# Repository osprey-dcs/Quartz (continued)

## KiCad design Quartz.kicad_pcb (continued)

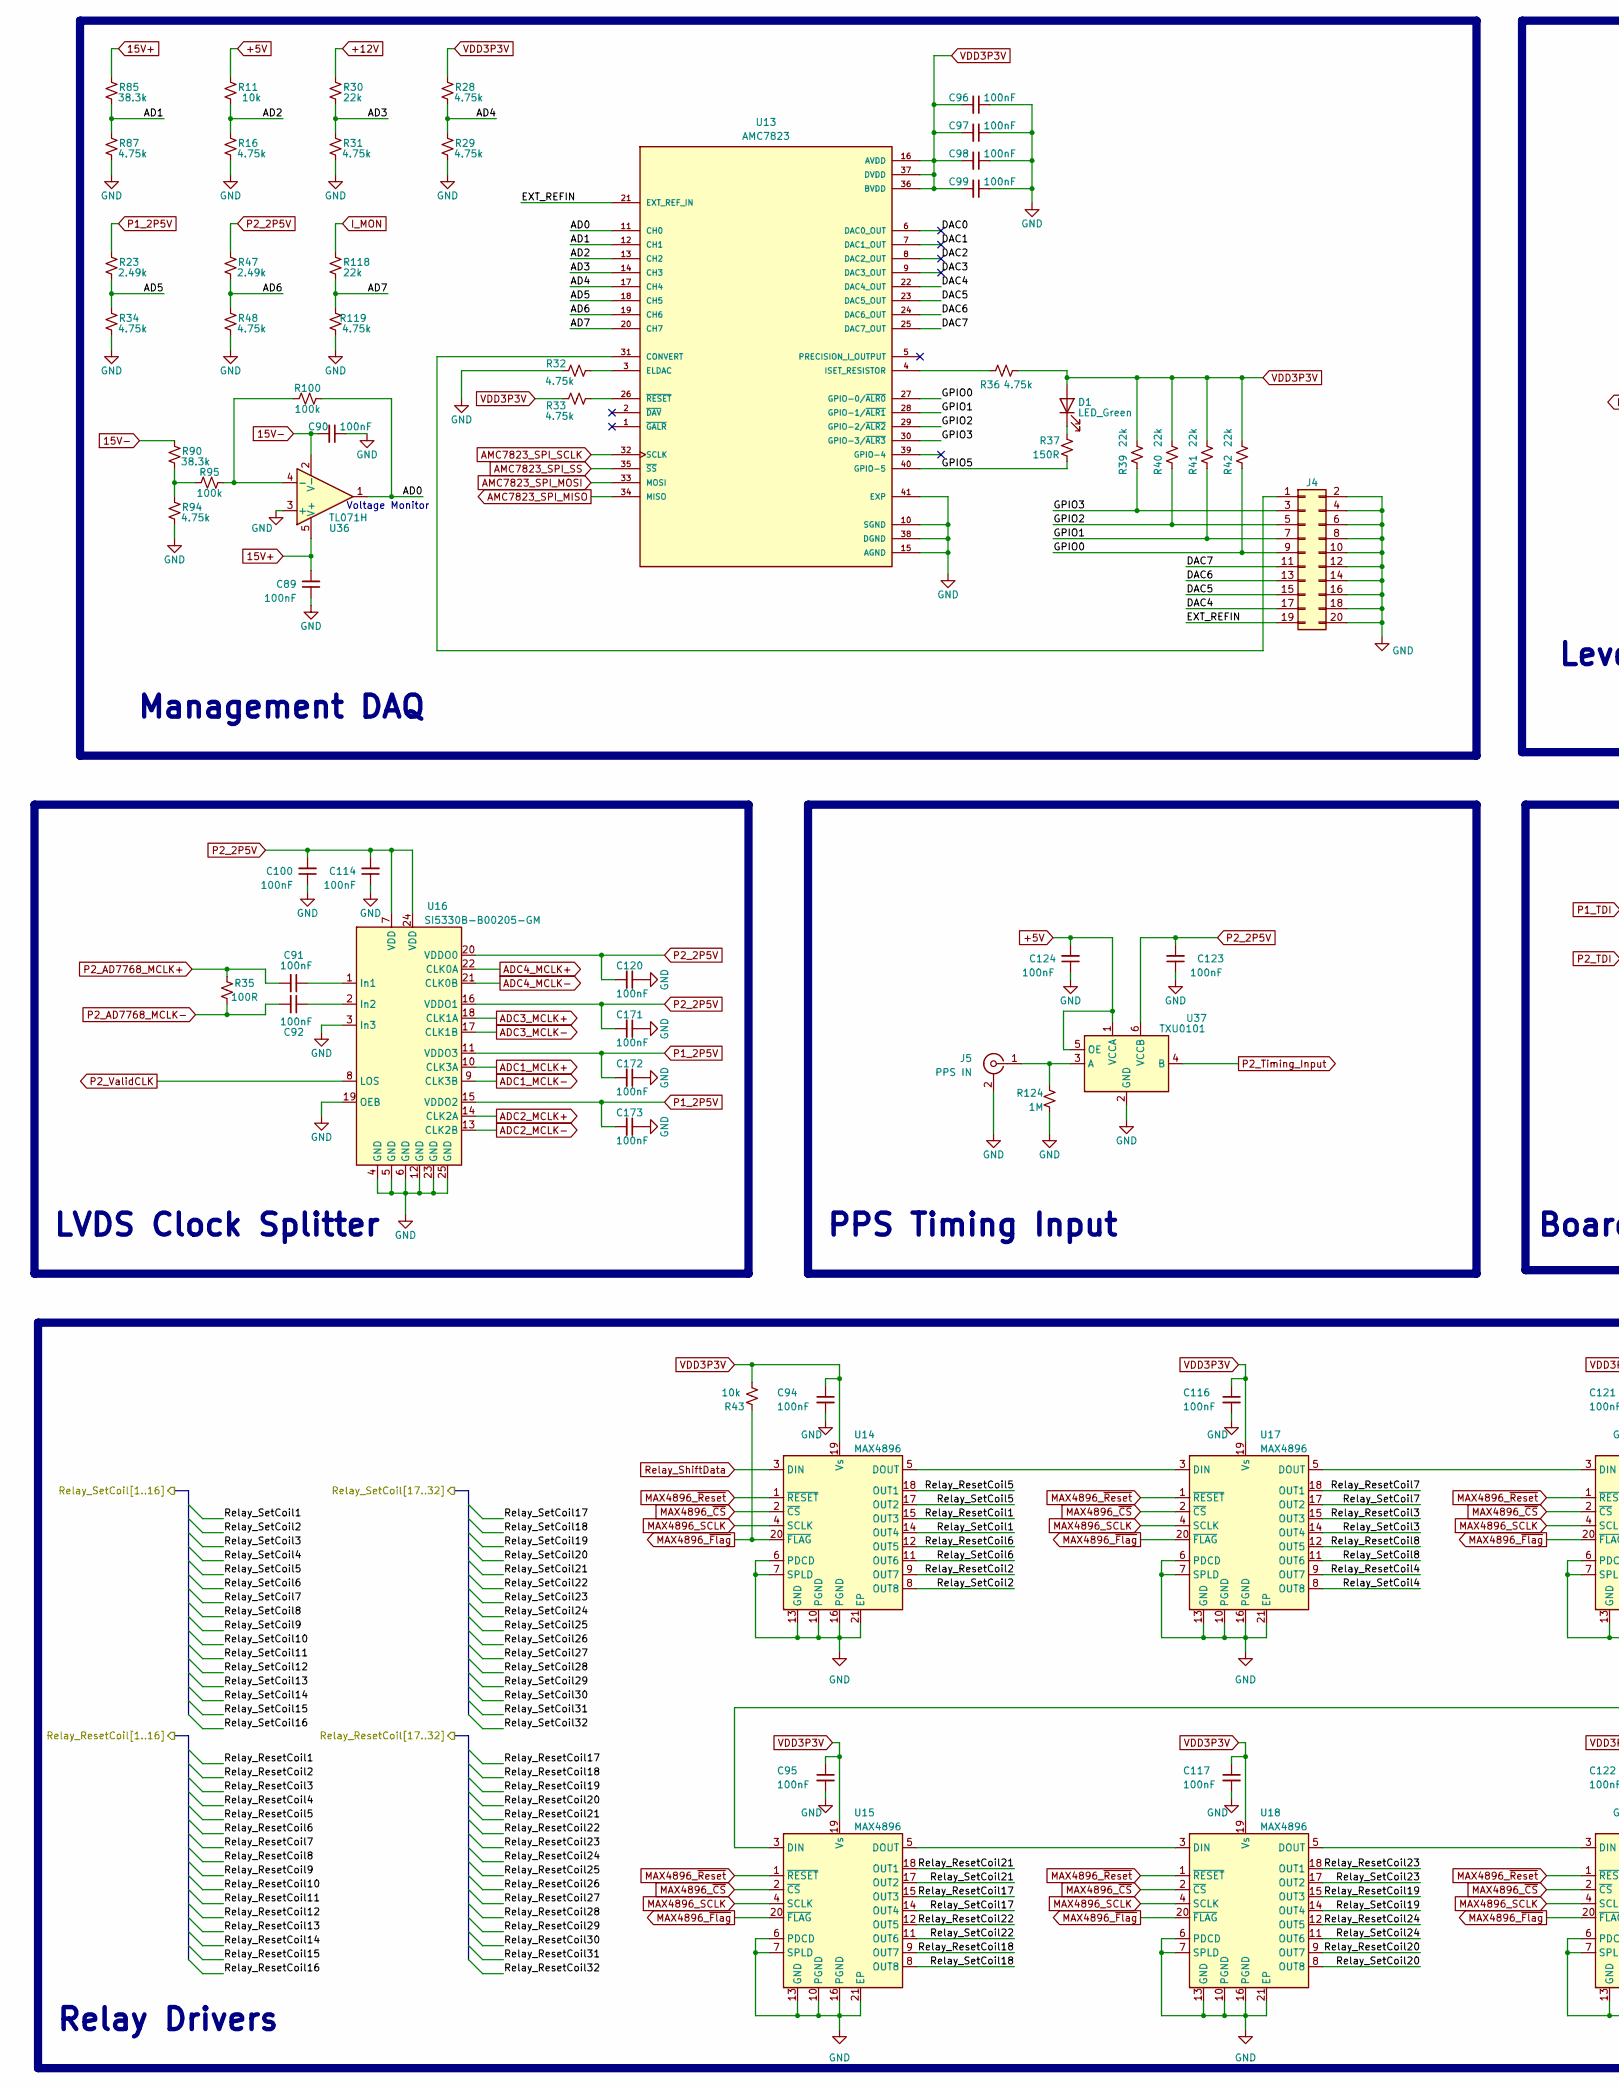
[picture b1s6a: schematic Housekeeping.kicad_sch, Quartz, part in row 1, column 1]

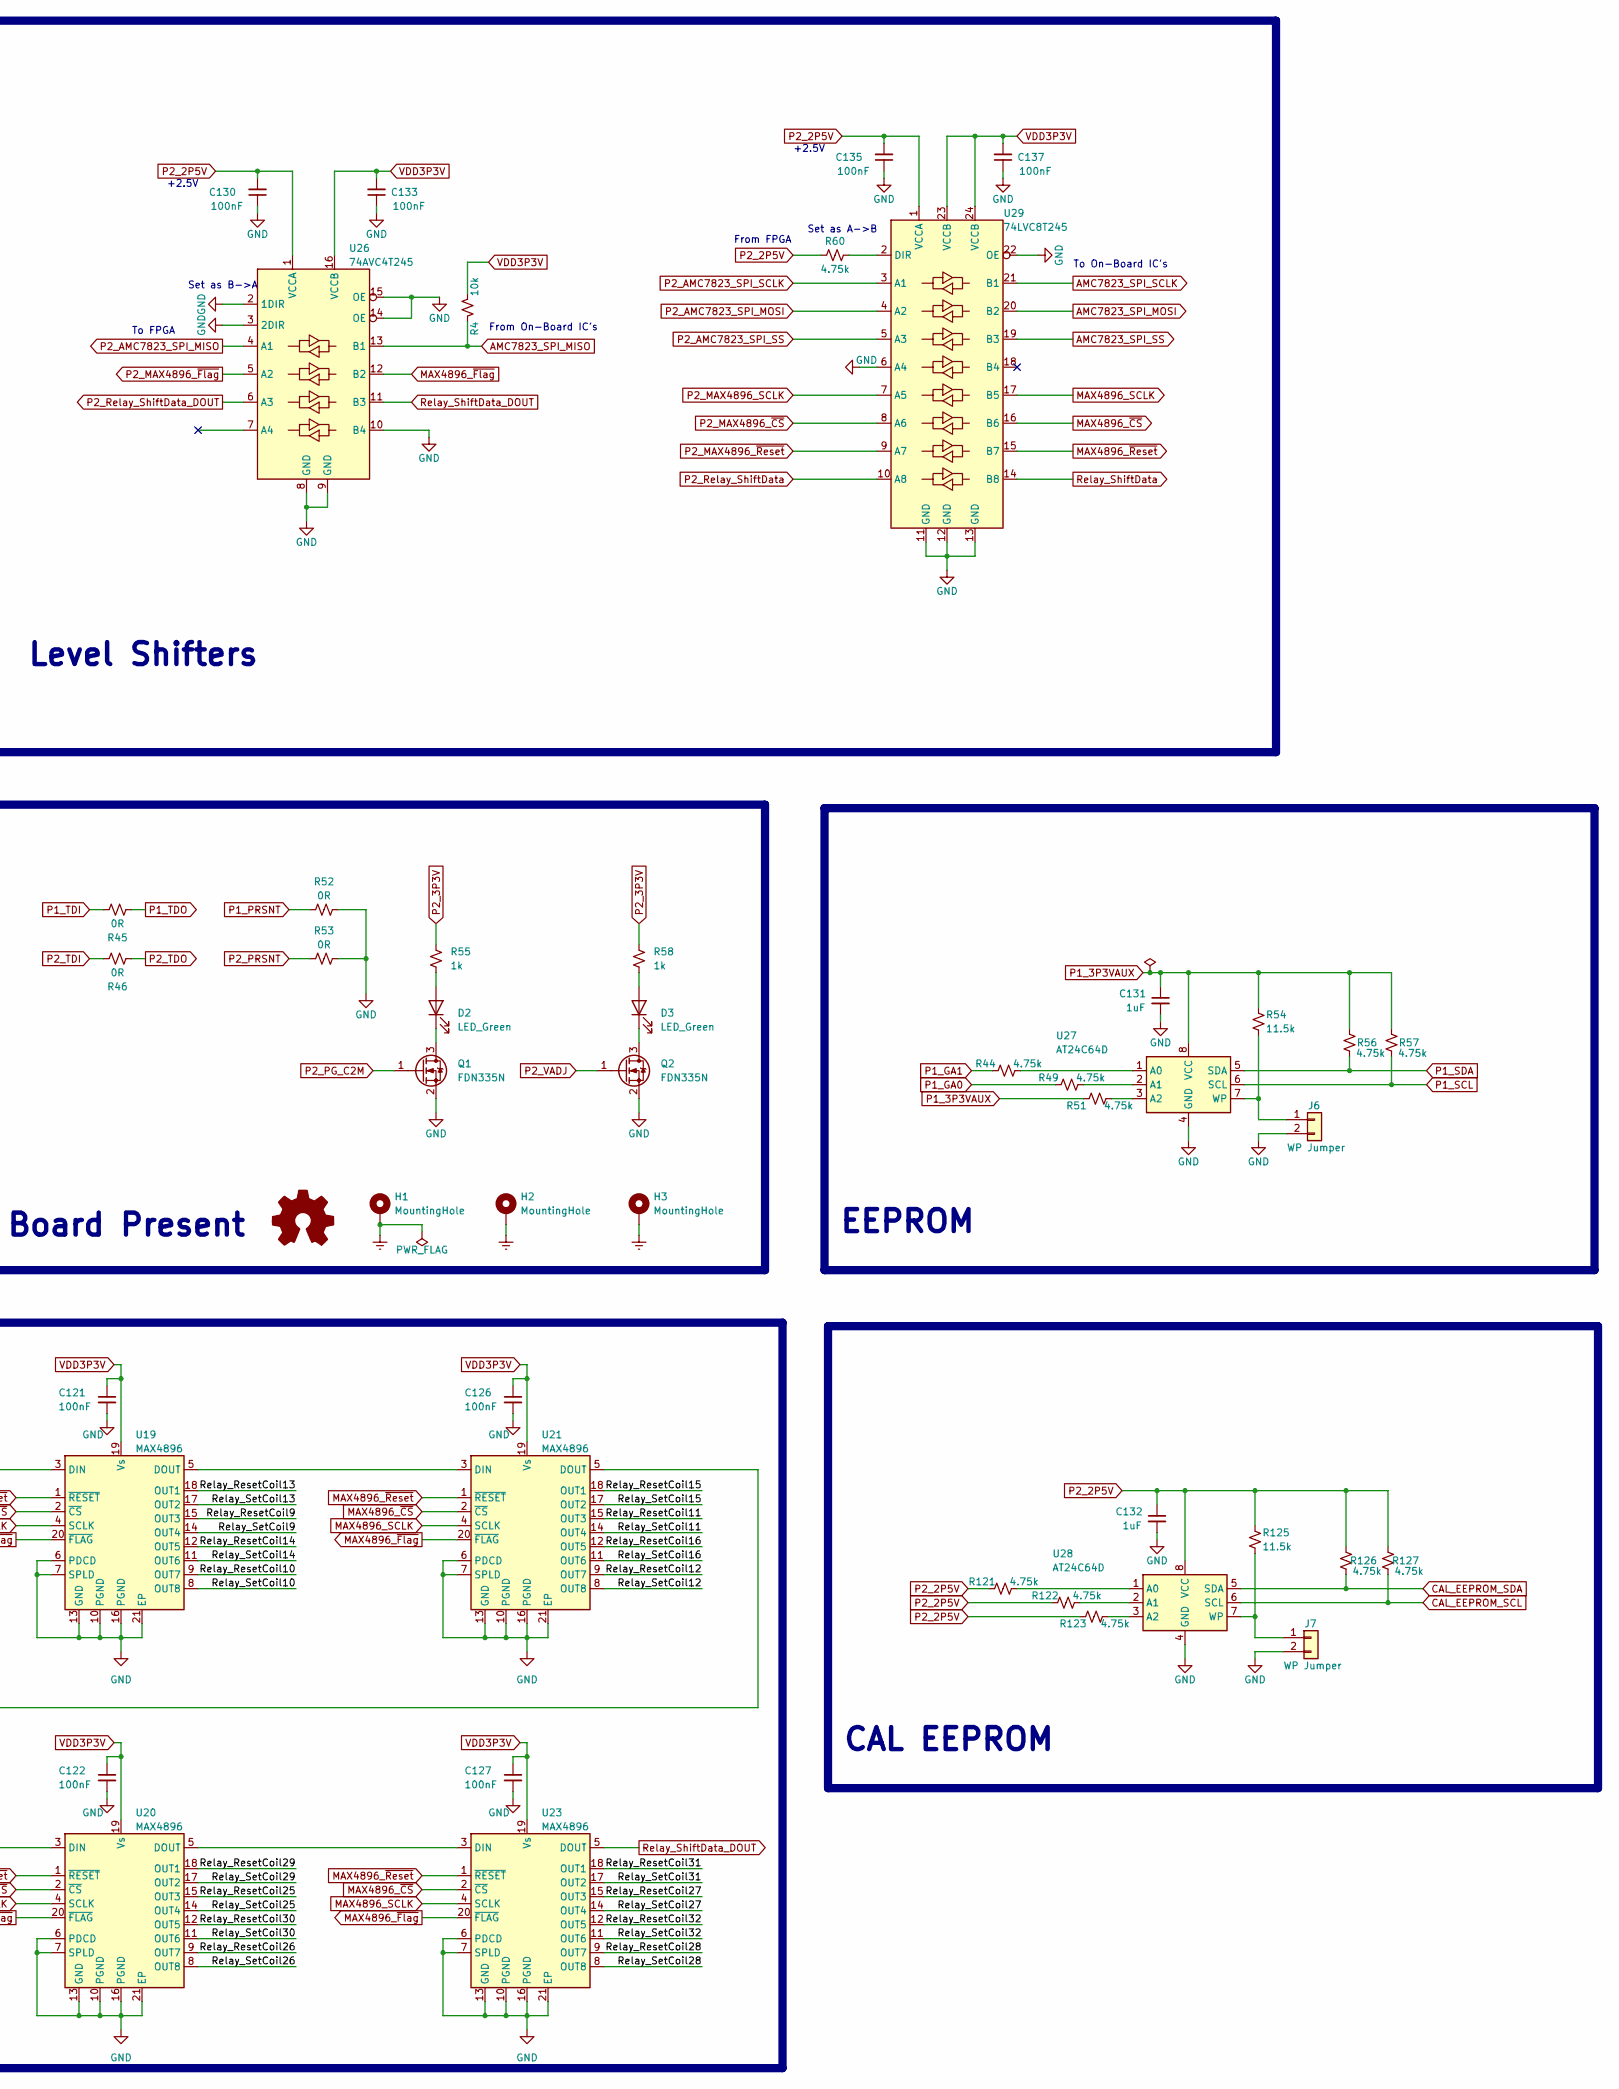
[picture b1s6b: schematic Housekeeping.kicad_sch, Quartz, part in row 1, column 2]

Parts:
C89, C90, C91, C92, C96, C97, C98, C99, C100, C114, C120, C123, C124, C130, C133, C135, C137, C171, C172, C173: 100nF; C_0402_1005Metric; MPN CL05A104KA5NNNC
C94, C95, C116, C117, C121, C122, C126, C127: 100nF; C_0603_1608Metric; MPN CL10B104KB8NNWC
C131, C132: 1uF; C_0603_1608Metric; MPN CC0603KRX7R7BB105
D1, D2, D3: LED_Green; LED_0603_1608Metric; MPN APT1608CGCK
H1, H2, H3: MountingHole; MountingHole_3mm_Pad
J4: Conn_02x10_Odd_Even; PinHeader_2x10_P1.27mm_Vertical_SMD; MPN M50-3601042R
J5: PPS IN; SMA_Amphenol_901-144_Vertical; MPN 901-144-8RFX
J6, J7: WP Jumper; PinHeader_1x02_P2.54mm_Vertical; MPN M20-9990245
Logo1: Logo_Open_Hardware_Small; Logo_2X
Q1, Q2: FDN335N; SOT-23; MPN FDN335N
R4, R43: 10k; R_0402_1005Metric; MPN RC0402FR-0710KL
R11: 10k; R_0603_1608Metric; MPN RC0603FR-0710KL
R16, R28, R29, R31, R32, R33, R34, R36, R48, R87, R94, R119: 4.75k; R_0603_1608Metric; MPN RC0603FR-074K75L
R23, R47: 2.49k; R_0603_1608Metric; MPN RC0603FR-072K49L
R30, R118: 22k; R_0603_1608Metric; MPN RC0603FR-0722KL
R35: 100R; R_0402_1005Metric; MPN RC0402FR-07100RL
R37: 150R; R_0603_1608Metric; MPN RC0603FR-07150RL
R39, R40, R41, R42: 22k; R_0402_1005Metric; MPN RC0402FR-0722KL
R44, R49, R51, R56, R57, R60, R121, R122, R123, R126, R127: 4.75k; R_0402_1005Metric; MPN RC0402FR-074K75L
R45, R46, R52, R53: 0R; R_0603_1608Metric; MPN ERJ-3GEY0R00V
R54, R125: 11.5k; R_0402_1005Metric; MPN RC0402FR-0711K5L
R55, R58: 1k; R_0603_1608Metric; MPN RC0603FR-071KL
R85, R90: 38.3k; R_0603_1608Metric; MPN RC0603FR-0738K3L
R95, R100: 100k; R_0603_1608Metric; MPN RC0603FR-07100KL
R124: 1M; R_0603_1608Metric; MPN CPF0603B1M0E1
U13: AMC7823; QFN-40-1EP_6x6mm_P0.5mm_EP4.6x4.6mm; MPN AMC7823IRTAT
U14, U15, U17, U18, U19, U20, U21, U23: MAX4896; TQFN-20-1EP_5x5mm_P0.65mm_EP3.1x3.1mm; MPN MAX4896ATP+
U16: SI5330B-B00205-GM; QFN-24-1EP_4x4mm_P0.5mm_EP2.6x2.6mm; MPN SI5330B-B00205-GM
U26: 74AVC4T245; TSSOP-16_4.4x5mm_P0.65mm; MPN SN74AVC4T245PWR
U27, U28: AT24C64D; SOIC-8_3.9x4.9mm_P1.27mm; MPN AT24C64D-SSHM-T
U29: 74LVC8T245; TSSOP-24_4.4x7.8mm_P0.65mm; MPN SN74LVC8T245PWR
U36: TL071H; SOT-23-5; MPN TL071HIDBVR
U37: TXU0101; SOT-23-6; MPN TXU0101DBVR

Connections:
15V+: C89.2, R85.1, U36.5 (V+); also elsewhere on the board
15V-: C90.2, R90.1, U36.2 (V-); also elsewhere on the board
+5V: C124.2, R11.1, U37.1 (VCCA), U37.5 (OE); also elsewhere on the board
+12V: R30.1; also elsewhere on the board
/Housekeeping/AD0: R100.2, U13.11 (CH0), U36.1
/Housekeeping/AD1: R85.2, R87.1, U13.12 (CH1)
/Housekeeping/AD2: R11.2, R16.1, U13.13 (CH2)
/Housekeeping/AD3: R30.2, R31.1, U13.14 (CH3)
/Housekeeping/AD4: R28.2, R29.1, U13.17 (CH4)
/Housekeeping/AD5: R23.2, R34.1, U13.18 (CH5)
/Housekeeping/AD6: R47.2, R48.1, U13.19 (CH6)
/Housekeeping/AD7: R118.2, R119.1, U13.20 (CH7)
/Housekeeping/DAC0: U13.6 (DAC0_OUT)
/Housekeeping/DAC1: U13.7 (DAC1_OUT)
/Housekeeping/DAC2: U13.8 (DAC2_OUT)
/Housekeeping/DAC3: U13.9 (DAC3_OUT)
/Housekeeping/DAC4: J4.17, U13.22 (DAC4_OUT)
/Housekeeping/DAC5: J4.15, U13.23 (DAC5_OUT)
/Housekeeping/DAC6: J4.13, U13.24 (DAC6_OUT)
/Housekeeping/DAC7: J4.11, U13.25 (DAC7_OUT)
/Housekeeping/EXT_REFIN: J4.19, U13.21 (EXT_REF_IN)
/Housekeeping/GPIO0: J4.9, R42.2, U13.27 (GPIO-0/~ALR0)
/Housekeeping/GPIO1: J4.7, R41.2, U13.28 (GPIO-1/~ALR1)
/Housekeeping/GPIO2: J4.5, R40.2, U13.29 (GPIO-2/~ALR2)
/Housekeeping/GPIO3: J4.3, R39.2, U13.30 (GPIO-3/~ALR3)
/Housekeeping/GPIO5: R37.1, U13.40 (GPIO-5)
/Relay_ResetCoil1: U14.15 (OUT3); also elsewhere on the board
/Relay_ResetCoil2: U14.9 (OUT7); also elsewhere on the board
/Relay_ResetCoil3: U17.15 (OUT3); also elsewhere on the board
/Relay_ResetCoil4: U17.9 (OUT7); also elsewhere on the board
/Relay_ResetCoil5: U14.18 (OUT1); also elsewhere on the board
/Relay_ResetCoil6: U14.12 (OUT5); also elsewhere on the board
/Relay_ResetCoil7: U17.18 (OUT1); also elsewhere on the board
/Relay_ResetCoil8: U17.12 (OUT5); also elsewhere on the board
/Relay_ResetCoil9: U19.15 (OUT3); also elsewhere on the board
/Relay_ResetCoil10: U19.9 (OUT7); also elsewhere on the board
/Relay_ResetCoil11: U21.15 (OUT3); also elsewhere on the board
/Relay_ResetCoil12: U21.9 (OUT7); also elsewhere on the board
/Relay_ResetCoil13: U19.18 (OUT1); also elsewhere on the board
/Relay_ResetCoil14: U19.12 (OUT5); also elsewhere on the board
/Relay_ResetCoil15: U21.18 (OUT1); also elsewhere on the board
/Relay_ResetCoil16: U21.12 (OUT5); also elsewhere on the board
/Relay_ResetCoil17: U15.15 (OUT3); also elsewhere on the board
/Relay_ResetCoil18: U15.9 (OUT7); also elsewhere on the board
/Relay_ResetCoil19: U18.15 (OUT3); also elsewhere on the board
/Relay_ResetCoil20: U18.9 (OUT7); also elsewhere on the board
/Relay_ResetCoil21: U15.18 (OUT1); also elsewhere on the board
/Relay_ResetCoil22: U15.12 (OUT5); also elsewhere on the board
/Relay_ResetCoil23: U18.18 (OUT1); also elsewhere on the board
/Relay_ResetCoil24: U18.12 (OUT5); also elsewhere on the board
/Relay_ResetCoil25: U20.15 (OUT3); also elsewhere on the board
/Relay_ResetCoil26: U20.9 (OUT7); also elsewhere on the board
/Relay_ResetCoil27: U23.15 (OUT3); also elsewhere on the board
/Relay_ResetCoil28: U23.9 (OUT7); also elsewhere on the board
/Relay_ResetCoil29: U20.18 (OUT1); also elsewhere on the board
/Relay_ResetCoil30: U20.12 (OUT5); also elsewhere on the board
/Relay_ResetCoil31: U23.18 (OUT1); also elsewhere on the board
/Relay_ResetCoil32: U23.12 (OUT5); also elsewhere on the board
/Relay_SetCoil1: U14.14 (OUT4); also elsewhere on the board
/Relay_SetCoil2: U14.8 (OUT8); also elsewhere on the board
/Relay_SetCoil3: U17.14 (OUT4); also elsewhere on the board
/Relay_SetCoil4: U17.8 (OUT8); also elsewhere on the board
/Relay_SetCoil5: U14.17 (OUT2); also elsewhere on the board
/Relay_SetCoil6: U14.11 (OUT6); also elsewhere on the board
/Relay_SetCoil7: U17.17 (OUT2); also elsewhere on the board
/Relay_SetCoil8: U17.11 (OUT6); also elsewhere on the board
/Relay_SetCoil9: U19.14 (OUT4); also elsewhere on the board
/Relay_SetCoil10: U19.8 (OUT8); also elsewhere on the board
/Relay_SetCoil11: U21.14 (OUT4); also elsewhere on the board
/Relay_SetCoil12: U21.8 (OUT8); also elsewhere on the board
/Relay_SetCoil13: U19.17 (OUT2); also elsewhere on the board
/Relay_SetCoil14: U19.11 (OUT6); also elsewhere on the board
/Relay_SetCoil15: U21.17 (OUT2); also elsewhere on the board
/Relay_SetCoil16: U21.11 (OUT6); also elsewhere on the board
/Relay_SetCoil17: U15.14 (OUT4); also elsewhere on the board
/Relay_SetCoil18: U15.8 (OUT8); also elsewhere on the board
/Relay_SetCoil19: U18.14 (OUT4); also elsewhere on the board
/Relay_SetCoil20: U18.8 (OUT8); also elsewhere on the board
/Relay_SetCoil21: U15.17 (OUT2); also elsewhere on the board
/Relay_SetCoil22: U15.11 (OUT6); also elsewhere on the board
/Relay_SetCoil23: U18.17 (OUT2); also elsewhere on the board
/Relay_SetCoil24: U18.11 (OUT6); also elsewhere on the board
/Relay_SetCoil25: U20.14 (OUT4); also elsewhere on the board
/Relay_SetCoil26: U20.8 (OUT8); also elsewhere on the board
/Relay_SetCoil27: U23.14 (OUT4); also elsewhere on the board
/Relay_SetCoil28: U23.8 (OUT8); also elsewhere on the board
/Relay_SetCoil29: U20.17 (OUT2); also elsewhere on the board
/Relay_SetCoil30: U20.11 (OUT6); also elsewhere on the board
/Relay_SetCoil31: U23.17 (OUT2); also elsewhere on the board
/Relay_SetCoil32: U23.11 (OUT6); also elsewhere on the board
ADC1_MCLK+: U16.10 (CLK3A); also elsewhere on the board
ADC1_MCLK-: U16.9 (CLK3B); also elsewhere on the board
ADC2_MCLK+: U16.14 (CLK2A); also elsewhere on the board
ADC2_MCLK-: U16.13 (CLK2B); also elsewhere on the board
ADC3_MCLK+: U16.18 (CLK1A); also elsewhere on the board
ADC3_MCLK-: U16.17 (CLK1B); also elsewhere on the board
ADC4_MCLK+: U16.22 (CLK0A); also elsewhere on the board
ADC4_MCLK-: U16.21 (CLK0B); also elsewhere on the board
AMC7823_SPI_MISO: R4.2, U13.34 (MISO), U26.13 (B1)
AMC7823_SPI_MOSI: U13.33 (MOSI), U29.20 (B2)
AMC7823_SPI_SCLK: U13.32 (SCLK), U29.21 (B1)
AMC7823_SPI_SS: U13.35 (~SS), U29.19 (B3)
CAL_EEPROM_SCL: R127.2, U28.6 (SCL); also elsewhere on the board
CAL_EEPROM_SDA: R126.2, U28.5 (SDA); also elsewhere on the board
Earth: H1.1, H2.1, H3.1; also elsewhere on the board
GND: C89.1, C90.1, C94.2, C95.2, C96.1, C97.1, C98.1, C99.1, C100.1, C114.1, C116.2, C117.2, C120.1, C121.2, C122.2, C123.1, C124.1, C126.2, C127.2, C130.1, C131.2, C132.2, C133.1, C135.1, C137.1, C171.1, C172.1, C173.1, J4.2, J4.4, J4.6, J4.8, J4.10, J4.12, J4.14, J4.16, J4.18, J4.20, J5.2 (Ext), J6.2, J7.2, Q1.2 (S), Q2.2 (S), R16.2, R29.2, R31.2, R32.2, R34.2, R48.2, R52.2, R53.2, R87.2, R94.2, R119.2, R124.2, U13.10 (SGND), U13.15 (AGND), U13.38 (DGND), U13.41 (EXP), U14.6 (PDCD), U14.7 (SPLD), U14.10 (PGND), U14.13 (GND), U14.16 (PGND), U14.21 (EP), U15.6 (PDCD), U15.7 (SPLD), U15.10 (PGND), U15.13 (GND), U15.16 (PGND), U15.21 (EP), U16.3 (In3), U16.4 (GND), U16.5 (GND), U16.6 (GND), U16.12 (GND), U16.19 (OEB), U16.23 (GND), U16.25 (GND), U17.6 (PDCD), U17.7 (SPLD), U17.10 (PGND), U17.13 (GND), U17.16 (PGND), U17.21 (EP), U18.6 (PDCD), U18.7 (SPLD), U18.10 (PGND), U18.13 (GND), U18.16 (PGND), U18.21 (EP), U19.6 (PDCD), U19.7 (SPLD), U19.10 (PGND), U19.13 (GND), U19.16 (PGND), U19.21 (EP), U20.6 (PDCD), U20.7 (SPLD), U20.10 (PGND), U20.13 (GND), U20.16 (PGND), U20.21 (EP), U21.6 (PDCD), U21.7 (SPLD), U21.10 (PGND), U21.13 (GND), U21.16 (PGND), U21.21 (EP), U23.6 (PDCD), U23.7 (SPLD), U23.10 (PGND), U23.13 (GND), U23.16 (PGND), U23.21 (EP), U26.2 (1DIR), U26.3 (2DIR), U26.8 (GND), U26.9 (GND), U26.10 (B4), U26.14 (OE), U26.15 (OE), U27.4 (GND), U28.4 (GND), U29.6 (A4), U29.11 (GND), U29.12 (GND), U29.13 (GND), U29.22 (OE), U36.3 (+), U37.2 (GND); also elsewhere on the board
I_MON: R118.1; also elsewhere on the board
MAX4896_SCLK: U14.4 (SCLK), U15.4 (SCLK), U17.4 (SCLK), U18.4 (SCLK), U19.4 (SCLK), U20.4 (SCLK), U21.4 (SCLK), U23.4 (SCLK), U29.17 (B5)
MAX4896_~CS: U14.2 (~CS), U15.2 (~CS), U17.2 (~CS), U18.2 (~CS), U19.2 (~CS), U20.2 (~CS), U21.2 (~CS), U23.2 (~CS), U29.16 (B6)
MAX4896_~Flag: R43.2, U14.20 (~FLAG), U15.20 (~FLAG), U17.20 (~FLAG), U18.20 (~FLAG), U19.20 (~FLAG), U20.20 (~FLAG), U21.20 (~FLAG), U23.20 (~FLAG), U26.12 (B2)
MAX4896_~Reset: U14.1 (~RESET), U15.1 (~RESET), U17.1 (~RESET), U18.1 (~RESET), U19.1 (~RESET), U20.1 (~RESET), U21.1 (~RESET), U23.1 (~RESET), U29.15 (B7)
unnamed: D1.1 (K), R37.2
unnamed: D2.2 (A), R55.1
unnamed: D2.1 (K), Q1.3 (D)
unnamed: D3.2 (A), R58.1
unnamed: D3.1 (K), Q2.3 (D)
unnamed: J4.1, U13.31 (CONVERT)
unnamed: J5.1 (In), R124.1, U37.3 (A)
unnamed: J6.1, R54.2, U27.7 (WP)
unnamed: J7.1, R125.2, U28.7 (WP)
unnamed: R90.2, R94.1, R95.1
unnamed: R32.1, U13.3 (ELDAC)
unnamed: R36.2, U13.4 (ISET_RESISTOR)
unnamed: R33.1, U13.26 (~RESET)
unnamed: U14.5 (DOUT), U17.3 (DIN)
unnamed: U15.3 (DIN), U21.5 (DOUT)
unnamed: U15.5 (DOUT), U18.3 (DIN)
unnamed: C91.1, U16.1 (In1)
unnamed: C92.1, U16.2 (In2)
unnamed: U17.5 (DOUT), U19.3 (DIN)
unnamed: U18.5 (DOUT), U20.3 (DIN)
unnamed: U19.5 (DOUT), U21.3 (DIN)
unnamed: U20.5 (DOUT), U23.3 (DIN)
unnamed: R44.2, U27.1 (A0)
unnamed: R49.2, U27.2 (A1)
unnamed: R51.2, U27.3 (A2)
unnamed: R121.2, U28.1 (A0)
unnamed: R122.2, U28.2 (A1)
unnamed: R123.2, U28.3 (A2)
unnamed: R60.1, U29.2 (DIR)
unnamed: R95.2, R100.1, U36.4 (-)
P1_2P5V: C172.2, C173.2, R23.1, U16.11 (VDDO3), U16.15 (VDDO2); also elsewhere on the board
P1_3P3VAUX: C131.1, R51.1, R54.1, R56.1, R57.1, U27.8 (VCC); also elsewhere on the board
P1_GA0: R49.1; also elsewhere on the board
P1_GA1: R44.1; also elsewhere on the board
P1_PRSNT: R52.1; also elsewhere on the board
P1_SCL: R57.2, U27.6 (SCL); also elsewhere on the board
P1_SDA: R56.2, U27.5 (SDA); also elsewhere on the board
P1_TDI: R45.2; also elsewhere on the board
P1_TDO: R45.1; also elsewhere on the board
P2_2P5V: C100.2, C114.2, C120.2, C123.2, C130.2, C132.1, C135.2, C171.2, R47.1, R60.2, R121.1, R122.1, R123.1, R125.1, R126.1, R127.1, U16.7 (VDD), U16.16 (VDDO1), U16.20 (VDDO0), U16.24 (VDD), U26.1 (VCCA), U28.8 (VCC), U29.1 (VCCA), U37.6 (VCCB); also elsewhere on the board
P2_3P3V: R55.2, R58.2; also elsewhere on the board
P2_AD7768_MCLK+: C91.2, R35.2; also elsewhere on the board
P2_AD7768_MCLK-: C92.2, R35.1; also elsewhere on the board
P2_AMC7823_SPI_MISO: U26.4 (A1); also elsewhere on the board
P2_AMC7823_SPI_MOSI: U29.4 (A2); also elsewhere on the board
P2_AMC7823_SPI_SCLK: U29.3 (A1); also elsewhere on the board
P2_AMC7823_SPI_SS: U29.5 (A3); also elsewhere on the board
P2_MAX4896_SCLK: U29.7 (A5); also elsewhere on the board
P2_MAX4896_~CS: U29.8 (A6); also elsewhere on the board
P2_MAX4896_~Flag: U26.5 (A2); also elsewhere on the board
P2_MAX4896_~Reset: U29.9 (A7); also elsewhere on the board
P2_PG_C2M: Q1.1 (G); also elsewhere on the board
P2_PRSNT: R53.1; also elsewhere on the board
P2_Relay_ShiftData: U29.10 (A8); also elsewhere on the board
P2_Relay_ShiftData_DOUT: U26.6 (A3); also elsewhere on the board
P2_TDI: R46.2; also elsewhere on the board
P2_TDO: R46.1; also elsewhere on the board
P2_Timing_Input: U37.4 (B); also elsewhere on the board
P2_VADJ: Q2.1 (G); also elsewhere on the board
P2_ValidCLK: U16.8 (LOS); also elsewhere on the board
Relay_ShiftData: U14.3 (DIN), U29.14 (B8)
Relay_ShiftData_DOUT: U23.5 (DOUT), U26.11 (B3)
VDD3P3V: C94.1, C95.1, C96.2, C97.2, C98.2, C99.2, C116.1, C117.1, C121.1, C122.1, C126.1, C127.1, C133.2, C137.2, D1.2 (A), R4.1, R28.1, R33.2, R36.1, R39.1, R40.1, R41.1, R42.1, R43.1, U13.16 (AVDD), U13.36 (BVDD), U13.37 (DVDD), U14.19 (Vs), U15.19 (Vs), U17.19 (Vs), U18.19 (Vs), U19.19 (Vs), U20.19 (Vs), U21.19 (Vs), U23.19 (Vs), U26.16 (VCCB), U29.23 (VCCB), U29.24 (VCCB); also elsewhere on the board

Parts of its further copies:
C28, C87: 100nF; C_0402_1005Metric; MPN CL05A104KA5NNNC

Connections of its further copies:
+5V: C28.1; also elsewhere on the board
GND: C28.2, C87.2; also elsewhere on the board
unnamed 577: C87.1; also elsewhere on the board

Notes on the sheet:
PPS Timing Input
Set as B->A
EEPROM
Voltage Monitor
CAL EEPROM
Set as A->B
Relay Drivers
From On-Board IC's
From FPGA
LVDS Clock Splitter
+2.5V
To FPGA
Level Shifters
Management DAQ
To On-Board IC's
Board Present

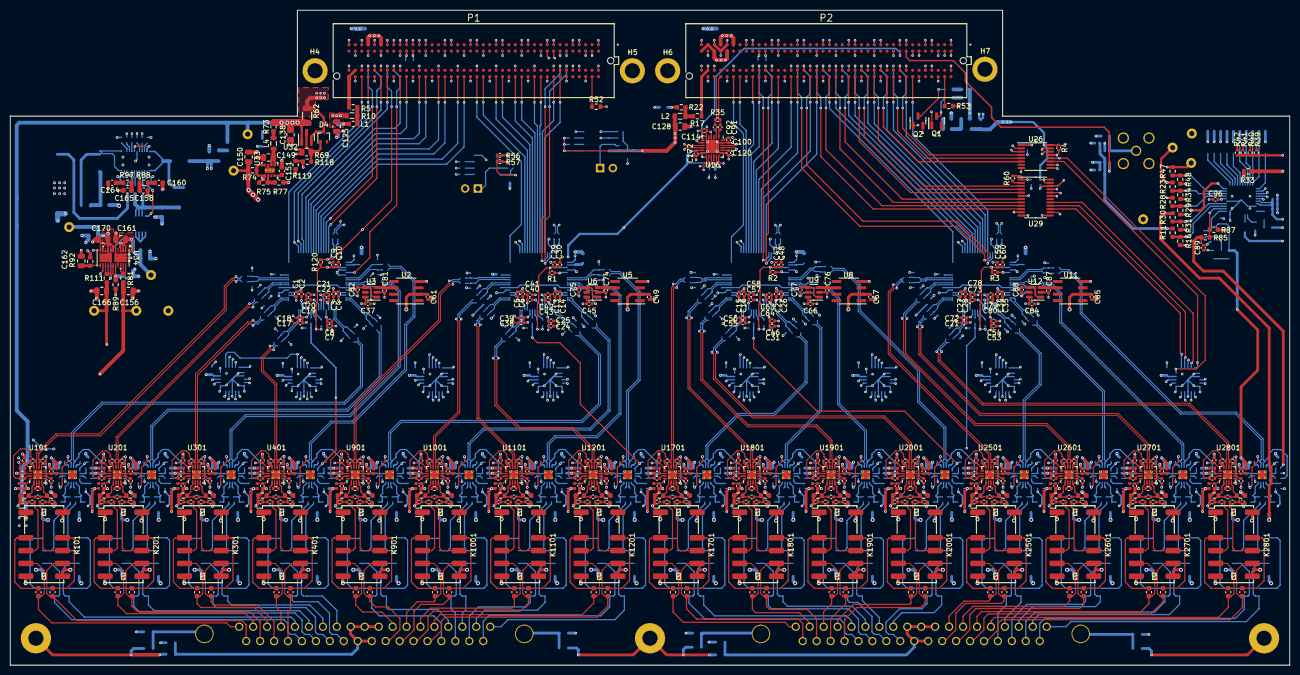
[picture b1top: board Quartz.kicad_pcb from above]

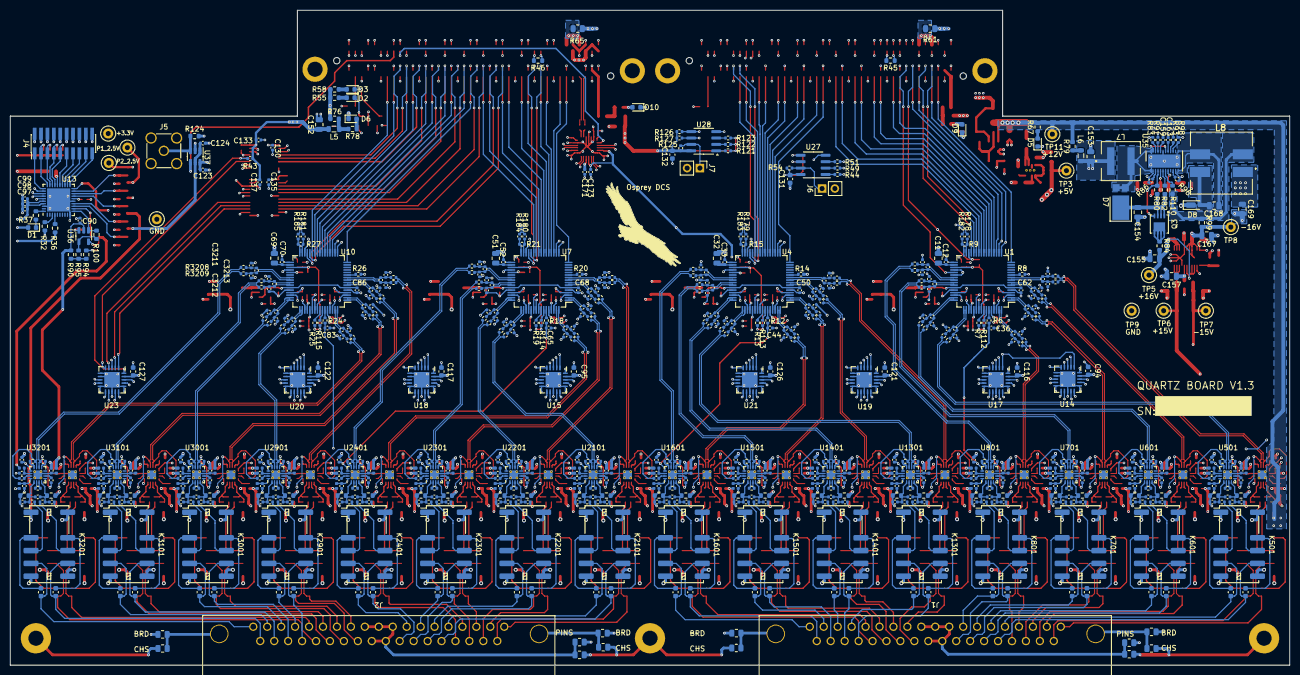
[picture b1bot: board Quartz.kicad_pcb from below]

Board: 6 copper layers, 254.0 x 130.0 mm, 1244 parts (709 on the bottom side), 998 nets.

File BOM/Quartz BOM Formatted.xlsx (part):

BOM: Quartz v1.2.1
Assembly Part Number/Revision: v1.2.1
Customer / Company Name: OspreyDCS
Item # | Quantity per board | Manufacturer Part # | Do Not Install | Reference designators | Value | Size / Footprint | Part description/ specs | Manfacturer
1 | 36 | CL05X105KP5NNNC |  | C1, C3, C5, C7, C9, C13, C15, C17, C19, C21, C23, C24, C27, C29, C31, C34, C38,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 | 1uF | Capacitor_SMD:C_0402_1005Metric | 1 µF ±10% 10V Ceramic Capacitor X6S 0402 (1005 Metric)
2 | 170 | CL05A104KA5NNNC |  | C2, C4, C6, C8, C10, C12, C14, C16, C18, C20, C22, C25, C26, C28, C30, C33, C35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 | 100nF | Capacitor_SMD:C_0402_1005Metric | 0.1 µF ±10% 25V Ceramic Capacitor X5R 0402 (1005 Metric)
3 | 4 | CL21A106KOQNNNE |  | C11, C32, C51, C69 | 10uF | Capacitor_SMD:C_0805_2012Metric | 10 µF ±10% 16V Ceramic Capacitor X5R 0805 (2012 Metric)
4 | 36 | CGA2B3X7R1H473K050BB |  | C36, C44, C65, C83, C108, C208, C308, C408, C508, C608, C708, C808, C908, C1008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 | 47nF | Capacitor_SMD:C_0402_1005Metric | 0.047 µF ±10% 50V Ceramic Capacitor X7R 0402 (1005 Metric)
5 | 8 | CL10B104KB8NNWC |  | C94, C95, C116, C117, C121, C122, C126, C127 | 100nF | Capacitor_SMD:C_0603_1608Metric | 0.1 µF ±10% 50V Ceramic Capacitor X7R 0603 (1608 Metric)
6 | 64 | C0603C103F3GAC7867 |  | C101, C102, C201, C202, C301, C302, C401, C402, C501, C502, C601, C602, C701, C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 | 10nF | Capacitor_SMD:C_0603_1608Metric | 10000 pF ±1% 25V Ceramic Capacitor C0G, NP0 0603 (1608 Metric)
7 | 96 | GRM1555C1H101JA01D |  | C109, C110, C113, C209, C210, C213, C309, C310, C313, C409, C410, C413, C509, C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 | 100pF | Capacitor_SMD:C_0402_1005Metric | 100 pF ±5% 50V Ceramic Capacitor C0G, NP0 0402 (1005 Metric)
8 | 64 | CC0402JRNPO9BN820 |  | C111, C112, C211, C212, C311, C312, C411, C412, C511, C512, C611, C612, C711, C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 | 82pF | Capacitor_SMD:C_0402_1005Metric | 82 pF ±5% 50V Ceramic Capacitor C0G, NP0 0402 (1005 Metric)
9 | 3 | C2012X5R1A476M125AC |  | C125, C128, C152 | 47uF | Capacitor_SMD:C_0805_2012Metric | 47 µF ±20% 10V Ceramic Capacitor X5R 0805 (2012 Metric)
10 | 1 | CC0603KRX7R7BB105 |  | C131 | 1uF | Capacitor_SMD:C_0603_1608Metric | 1 µF ±10% 16V Ceramic Capacitor X7R 0603 (1608 Metric)
11 | 4 | GRT21BR61E226ME13L |  | C138, C150, C156, C166 | 22uF | Capacitor_SMD:C_0805_2012Metric | 22 µF ±20% 25V Ceramic Capacitor X5R 0805 (2012 Metric)
12 | 7 | GRM21BR61E106KA73L |  | C149, C153, C154, C155, C167, C169, C170 | 10uF | Capacitor_SMD:C_0805_2012Metric | 10 µF ±10% 25V Ceramic Capacitor X5R 0805 (2012 Metric)
13 | 1 | GRM1885C1H332JA01D |  | C151 | 3.3nF | Capacitor_SMD:C_0603_1608Metric | 3300 pF ±5% 50V Ceramic Capacitor C0G, NP0 0603 (1608 Metric)
14 | 3 | TMK212AB7475KG-T |  | C157, C161, C162 | 4.7uF | Capacitor_SMD:C_0805_2012Metric | 4.7 µF ±10% 25V Ceramic Capacitor X7R 0805 (2012 Metric)
15 | 2 | GRM1885C1H470JA01D |  | C158, C165 | 47pF | Capacitor_SMD:C_0603_1608Metric | 47 pF ±5% 50V Ceramic Capacitor C0G, NP0 0603 (1608 Metric)
16 | 1 | CGA3E2C0G1H472J080AA |  | C160 | 4.7nF | Capacitor_SMD:C_0603_1608Metric | 4700 pF ±5% 50V Ceramic Capacitor C0G, NP0 0603 (1608 Metric)
17 | 1 | GCM1885C1H222JA16D |  | C164 | 2.2nF | Capacitor_SMD:C_0603_1608Metric | 2200 pF ±5% 50V Ceramic Capacitor C0G, NP0 0603 (1608 Metric)
18 | 1 | GRM21BR71E225KE11L |  | C168 | 2.2uF | Capacitor_SMD:C_0805_2012Metric | 2.2 µF ±10% 25V Ceramic Capacitor X7R 0805 (2012 Metric)
19 | 7 | APT1608CGCK |  | D1, D2, D3, D5, D6, D9, D10 | LED_Green | LED_SMD:LED_0603_1608Metric | Green 570nm LED Indication - Discrete 2.1V 0603 (1608 Metric)
20 | 1 | BAT54W-7-F |  | D4 | BAT54W | Package_TO_SOT_SMD:SOT-323_SC-70 | Diode 30 V 200mA Surface Mount SOT-323
21 | 1 | PDS360Q-13 |  | D7 | PDS360Q-13 | QuartzFootprints:D_PowerDI-5 | DIODE SCHOTTKY 60V 3A POWERDI5
22 | 1 | PD3S230H-7 |  | D8 | PD3S230H | QuartzFootprints:D_SOD-323_HandSoldering | Diode 30 V 2A Surface Mount PowerDI™ 323
23 | 2 | 5747847-6 |  | J1, J2 | DB37 | QuartzFootprints:CONN_5747847-6_TYC | 37 Position D-Sub Receptacle, Female Sockets Connector
24 | 1 | M50-3601042R |  | J4 | Conn_02x10_Odd_Even | Connector_PinHeader_1.27mm:PinHeader_2x10_P1.27mm_Vertical_SMD | Connector Header Surface Mount 20 position 0.050" (1.27mm)
25 | 1 | 901-144-8RFX |  | J5 | PPS IN | QuartzFootprints:SMA_Amphenol_901-144_Vertical | SMA Connector Jack, Female Socket 50 Ohms Through Hole Solder
26 | 1 | M22-2510205 |  | J6 | WP Jumper | Connector_PinHeader_2.00mm:PinHeader_1x02_P2.00mm_Vertical | Connector Header Through Hole 2 position 0.079" (2.00mm)
27 | 32 | EE2-12TNU-L |  | K101, K201, K301, K401, K501, K601, K701, K801, K901, K1001, K1101, K1201, K130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 | EE2-12TNU-L | QuartzFootprints:Relay_DPDT_Kemet_EE2_NU_DoubleCoil | General Purpose Relay DPDT (2 Form C) Surface Mount
28 | 5 | BLM21PG600SN1D |  | L1, L2, L4, L5, L6 | 60R@100Mhz; 3.5A | Inductor_SMD:L_0805_2012Metric | 60 Ohms @ 100 MHz 1 Power Line Ferrite Bead 0805 (2012 Metric) 3.5A 20mOhm
29 | 1 | XAL6060-682MEC |  | L7 | 6.8uH | QuartzFootprints:IND_7345-WE-PD_WRE | Power Inductors - SMD 6.8uH Shld 20% 9A 20.8mOhms AECQ2
30 | 1 | MSD1260-153MLD |  | L8 | 15uH | QuartzFootprints:MSD1260153MLD | Coupled Inductors 15uH Shld 20% 2.92A 85mOhm
31 | 96 | BLM15AX601SN1D |  | L101, L102, L103, L201, L202, L203, L301, L302, L303, L401, L402, L403, L501, L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 | 600R | Inductor_SMD:L_0402_1005Metric | 600 Ohms @ 100 MHz 1 Ferrite Bead 0402 (1005 Metric) 500mA 340mOhm
32 | 2 | ASP-134604-01 |  | P1, P2 | ASP-134604-01 | QuartzFootprints:SAMTEC_ASP-134604-01 | Board to Board & Mezzanine Connectors "ASP"
33 | 2 | FDN335N |  | Q1, Q2 | FDN335N | Package_TO_SOT_SMD:SOT-23 | N-Channel 20 V 1.7A (Ta) 500mW (Ta) Surface Mount SOT-23-3
34 | 1 | FDMC510P |  | Q3 | FDMC510P | QuartzFootprints:MLP8_3P3X3P3_ONS-M | P-Channel 20 V 12A (Ta), 18A (Tc) 2.3W (Ta), 41W (Tc) Surface Mount 8-MLP (3.3x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
35 | 21 | RC0402FR-074K75L |  | R1, R2, R3, R7, R8, R13, R14, R19, R20, R25, R26, R44, R49, R51, R56, R57, R60,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 | 4.75k | Resistor_SMD:R_0402_1005Metric | 4.75 kOhms ±1% 0.063W, 1/16W Chip Resistor 0402 (1005 Metric) Moisture Resistan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
36 | 2 | RC0402FR-0710KL |  | R4, R43 | 10k | Resistor_SMD:R_0402_1005Metric | 10 kOhms ±1% 0.063W, 1/16W Chip Resistor 0402 (1005 Metric) Moisture Resistant 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
37 | 14 | ERJ-3GEY0R00V |  | R5, R17, R45, R46, R52, R53, R73, R74, R76, R79, R81, R84, R99, R111 | 0R | Resistor_SMD:R_0603_1608Metric | 0 Ohms Jumper Chip Resistor 0603 (1608 Metric) Automotive AEC-Q200 Thick Film
38 | 4 | RC0402FR-0749R9L |  | R6, R12, R18, R24 | 49.9R | Resistor_SMD:R_0402_1005Metric | 49.9 Ohms ±1% 0.063W, 1/16W Chip Resistor 0402 (1005 Metric) Moisture Resistant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
39 | 5 | RC0402FR-07100RL |  | R9, R15, R21, R27, R35 | 100R | Resistor_SMD:R_0402_1005Metric | 100 Ohms ±1% 0.063W, 1/16W Chip Resistor 0402 (1005 Metric) Moisture Resistant 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
40 | 5 | RC0603FR-071KL |  | R10, R22, R55, R58, R78 | 1k | Resistor_SMD:R_0603_1608Metric | 1 kOhms ±1% 0.1W, 1/10W Chip Resistor 0603 (1608 Metric) Moisture Resistant Thi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
41 | 1 | RC0603FR-0710KL |  | R11 | 10k | Resistor_SMD:R_0603_1608Metric | 10 kOhms ±1% 0.1W, 1/10W Chip Resistor 0603 (1608 Metric) Moisture Resistant Th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
42 | 12 | RC0603FR-074K75L |  | R16, R28, R29, R31, R32, R33, R34, R36, R48, R87, R94, R119 | 4.75k | Resistor_SMD:R_0603_1608Metric | 4.75 kOhms ±1% 0.1W, 1/10W Chip Resistor 0603 (1608 Metric) Moisture Resistant 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
43 | 2 | RC0603FR-072K49L |  | R23, R47 | 2.49k | Resistor_SMD:R_0603_1608Metric | 2.49 kOhms ±1% 0.1W, 1/10W Chip Resistor 0603 (1608 Metric) Moisture Resistant 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
44 | 2 | RC0603FR-0722KL |  | R30, R118 | 22k | Resistor_SMD:R_0603_1608Metric | 22 kOhms ±1% 0.1W, 1/10W Chip Resistor 0603 (1608 Metric) Moisture Resistant Th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
45 | 1 | RC0603FR-07150RL |  | R37 | 150R | Resistor_SMD:R_0603_1608Metric | 150 Ohms ±1% 0.1W, 1/10W Chip Resistor 0603 (1608 Metric) Moisture Resistant Th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
46 | 4 | RC0402FR-0722KL |  | R39, R40, R41, R42 | 22k | Resistor_SMD:R_0402_1005Metric | 22 kOhms ±1% 0.063W, 1/16W Chip Resistor 0402 (1005 Metric) Moisture Resistant 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
